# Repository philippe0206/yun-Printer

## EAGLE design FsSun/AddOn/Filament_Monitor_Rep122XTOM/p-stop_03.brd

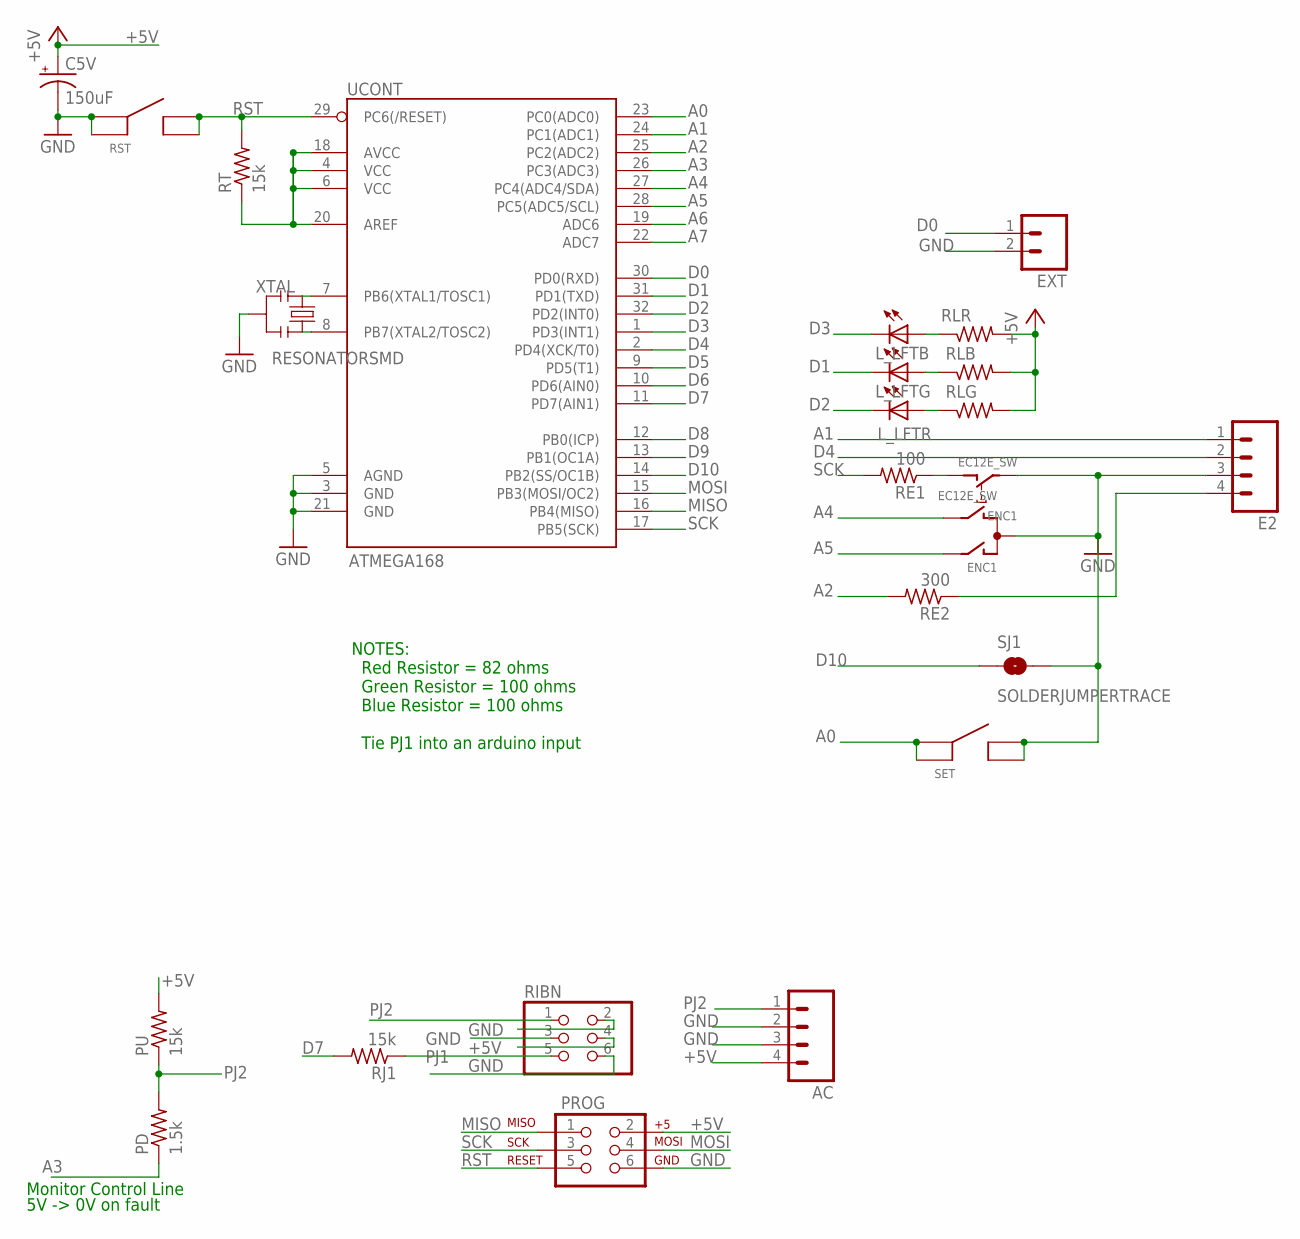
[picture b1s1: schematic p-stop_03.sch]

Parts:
AC: M04PTH; 1X04
C5V: 150uF; EIA3528
E2: M04PTH; 1X04
ENC1: EC12E_SW; ALPS_EC12E_SW
EXT: M02PTH; 1X02
L_LFT: GM5WA94310A
PD: 1.5k; MINI_MELF-0204R
PROG: AVR_SPI_PRG_6NS; 2X3-NS
PU: 15k; MINI_MELF-0204R
RE1: 100; MINI_MELF-0204R
RE2: 300; MINI_MELF-0204R
RIBN: PINHD-2X3; 2X03
RJ1: 15k; MINI_MELF-0204R
RLB: 100; MINI_MELF-0204R
RLG: 100; MINI_MELF-0204R
RLR: 100; MINI_MELF-0204R
RST: 6MM_TACT_SMD; 6MMSMDTACT
RT: 15k; MINI_MELF-0204R
SET: 6MM_TACT_SMD; 6MMSMDTACT
SJ1: SOLDERJUMPERTRACE; SJ_2S-TRACE
UCONT: ATMEGA168; TQFP32-08
XTAL: RESONATORSMD; RESONATOR-SMD

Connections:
+5V: AC.4, C5V.A (+), PROG.2, PU.2, RIBN.4, RLB.2, RLG.2, RLR.2, RT.1, UCONT.4 (VCC), UCONT.6 (VCC), UCONT.18 (AVCC), UCONT.20 (AREF)
A0: SET.P1, SET.P2, UCONT.23 (PC0(ADC0))
A1: E2.1, UCONT.24 (PC1(ADC1))
A2: RE2.2, UCONT.25 (PC2(ADC2))
A3: PD.1, UCONT.26 (PC3(ADC3))
A4: ENC1.B, UCONT.27 (PC4(ADC4/SDA))
A5: ENC1.A, UCONT.28 (PC5(ADC5/SCL))
A6: UCONT.19 (ADC6)
A7: UCONT.22 (ADC7)
D0: EXT.1, UCONT.30 (PD0(RXD))
D1: L_LFT.4 (C), UCONT.31 (PD1(TXD))
D2: L_LFT.5 (C), UCONT.32 (PD2(INT0))
D3: L_LFT.6 (C), UCONT.1 (PD3(INT1))
D4: E2.2, UCONT.2 (PD4(XCK/T0))
D5: UCONT.9 (PD5(T1))
D6: UCONT.10 (PD6(AIN0))
D7: RJ1.2, UCONT.11 (PD7(AIN1))
D8: UCONT.12 (PB0(ICP))
D9: UCONT.13 (PB1(OC1A))
D10: SJ1.1, UCONT.14 (PB2(SS/OC1B))
ENC2L: E2.4, RE2.1
GND: AC.2, AC.3, C5V.C (-), E2.3, ENC1.C, ENC1.E (2), EXT.2, PROG.6, RIBN.2, RIBN.3, RIBN.6, RST.P1, RST.P2, SET.N1, SET.N2, SJ1.2, UCONT.3 (GND), UCONT.5 (AGND), UCONT.21 (GND), XTAL.2
MISO: PROG.1, UCONT.16 (PB4(MISO))
MOSI: PROG.4, UCONT.15 (PB3(MOSI/OC2))
unnamed: UCONT.7 (PB6(XTAL1/TOSC1)), XTAL.1
unnamed: UCONT.8 (PB7(XTAL2/TOSC2)), XTAL.3
unnamed: ENC1.D (1), RE1.1
unnamed: L_LFT.1 (A), RLR.1
unnamed: L_LFT.3 (A), RLB.1
unnamed: L_LFT.2 (A), RLG.1
PJ1: RIBN.5, RJ1.1
PJ2: AC.1, PD.2, PU.1, RIBN.1
RST: PROG.5, RST.N1, RST.N2, RT.2, UCONT.29 (PC6(/RESET))
SCK: PROG.3, RE1.2, UCONT.17 (PB5(SCK))

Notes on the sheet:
NOTES: Red Resistor = 82 ohms Green Resistor = 100 ohms Blue Resistor = 100 ohms Tie PJ1 into an arduino input
Monitor Control Line
5V -> 0V on fault

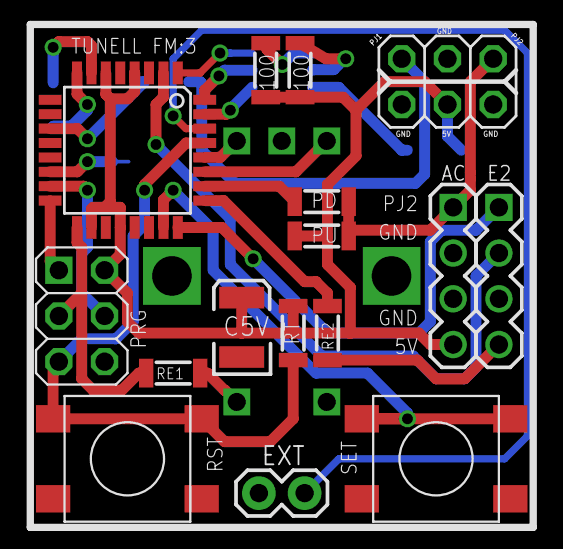
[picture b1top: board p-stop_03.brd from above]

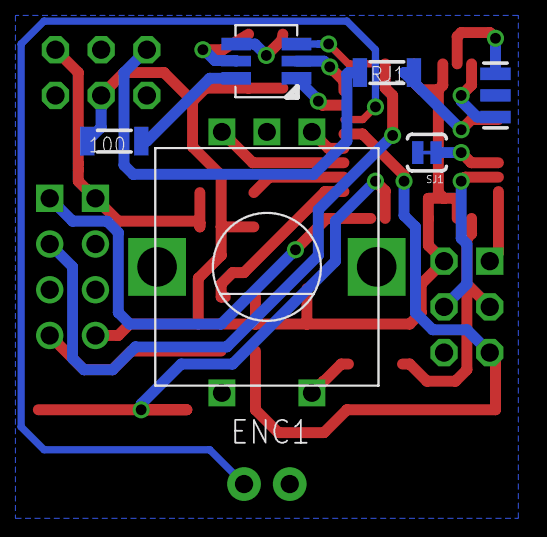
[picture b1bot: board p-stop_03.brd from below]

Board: 2 copper layers, 22 parts (6 on the bottom side), 28 nets.

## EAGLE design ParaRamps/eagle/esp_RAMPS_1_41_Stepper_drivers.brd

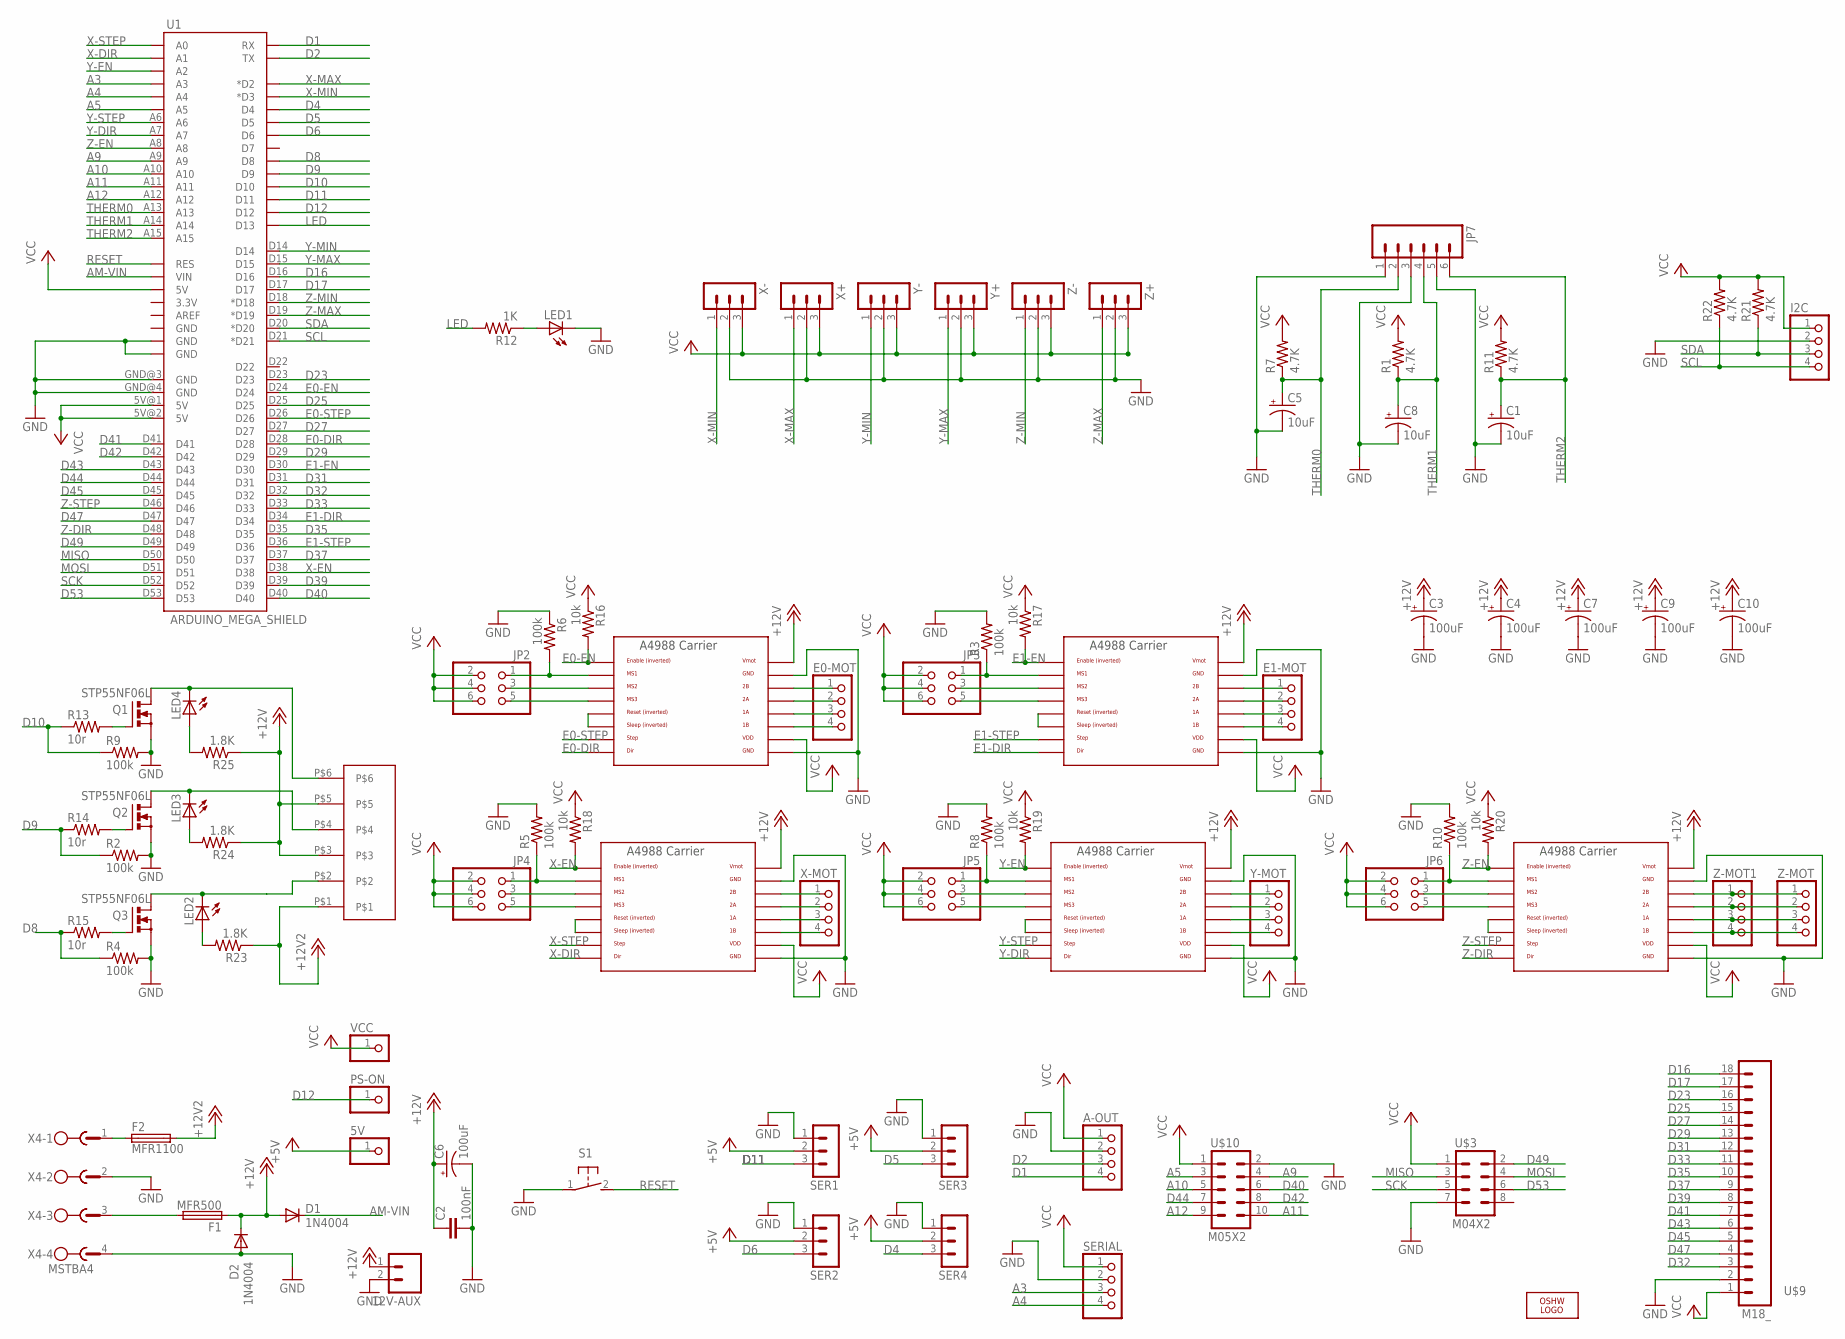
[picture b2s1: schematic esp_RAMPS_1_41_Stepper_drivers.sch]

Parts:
5V: PINHD-1X1; 1X01
12V-AUX: M02PTH; 1X02
A-OUT: PINHD-1X4; 1X04
C1, C5, C8: 10uF; 153CLV-0405
C2: 100nF; C0805
C3, C4, C6, C7, C9, C10: 100uF; 153CLV-0605
D1, D2: 1N4004; DO41-10
E0-MOT, E1-MOT: PINHD-1X4; 1X04
F1: MFR500
F2: MFR1100
I2C: PINHD-1X4; 1X04
JP2, JP3, JP4, JP5, JP6: PINHD-2X3; 2X03
JP7: M06SIP; 1X06
LED1, LED2, LED3, LED4: LEDCHIP-LED0805; CHIP-LED0805
LOGO1: OSHW_LOGO_6MILX0100-NT; OSHW_6X100_NOTEXT
PS-ON: PINHD-1X1; 1X01
Q1, Q2, Q3: STP55NF06L; TO220BV
R1, R7, R11, R21, R22: 4.7K; R0805
R2, R3, R4, R5, R6, R8, R9, R10: 100k; R0805
R12: 1K; R0805
R13, R15: 10r; R0805
R14: 10r; M0805
R16, R17, R18, R19, R20: 10k; R0805
R23, R24, R25: 1.8K; R0805
S1: 31-XX; B3F-31XX
SER1, SER2, SER3, SER4: 3PIN-HEADER
SERIAL: PINHD-1X4; 1X04
U1: ARDUINO_MEGA_SHIELD
U$2: 282837-6
U$3: M04X2; 2X4
U$4, U$5, U$6, U$7, U$8: A4988BREAKOUT
U$9: M18_; 1X18
U$10: M05X2; 2X5
VCC: PINHD-1X1; 1X01
X4: MSTBA4
X+: 3PIN-HEADER
X-: 3PIN-HEADER
X-MOT: PINHD-1X4; 1X04
Y+: 3PIN-HEADER
Y-: 3PIN-HEADER
Y-MOT: PINHD-1X4; 1X04
Z+: 3PIN-HEADER
Z-: 3PIN-HEADER
Z-MOT, Z-MOT1: PINHD-1X4; 1X04

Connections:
+5V: 5V.1, SER1.2, SER2.2, SER3.2, SER4.2
+12V: 12V-AUX.1, C2.1, C3.+, C4.+, C6.+, C7.+, C9.+, C10.+, D1.A, D2.C, F1.1, R24.1, R25.1, U$2.P$3, U$2.P$5, U$4.VMOT, U$5.VMOT, U$6.VMOT, U$7.VMOT, U$8.VMOT
+12V2: F2.2, R23.1, U$2.P$1
A3: SERIAL.3, U1.A3
A4: SERIAL.4, U1.A4
A5: U1.A5, U$10.3
A9: U1.A9, U$10.4
A10: U1.A10, U$10.5
A11: U1.A11, U$10.10
A12: U1.A12, U$10.9
AM-VIN: D1.C, U1.VIN
D1: A-OUT.4, U1.RX
D2: A-OUT.3, U1.TX
D4: SER4.3, U1.D4
D5: SER3.3, U1.D5
D6: SER2.3, U1.D6
D8: R4.1, R15.1, U1.D8
D9: R2.1, R14.1, U1.D9
D10: R9.1, R13.1, U1.D10
D11: SER1.3, U1.D11
D12: PS-ON.1, U1.D12
D16: U1.D16, U$9.18
D17: U1.D17, U$9.17
D23: U1.D23, U$9.16
D25: U1.D25, U$9.15
D27: U1.D27, U$9.14
D29: U1.D29, U$9.13
D31: U1.D31, U$9.12
D32: U1.D32, U$9.3
D33: U1.D33, U$9.11
D35: U1.D35, U$9.10
D37: U1.D37, U$9.9
D39: U1.D39, U$9.8
D40: U1.D40, U$10.6
D41: U1.D41, U$9.7
D42: U1.D42, U$10.8
D43: U1.D43, U$9.6
D44: U1.D44, U$10.7
D45: U1.D45, U$9.5
D47: U1.D47, U$9.4
D49: U1.D49, U$3.2
D53: U1.D53, U$3.6
E0-DIR: U1.D28, U$4.DIR
E0-EN: R16.2, U1.D24, U$4.EN
E0-STEP: U1.D26, U$4.STEP
E1-DIR: U1.D34, U$5.DIR
E1-EN: R17.2, U1.D30, U$5.EN
E1-STEP: U1.D36, U$5.STEP
GND: 12V-AUX.2, A-OUT.2, C1.-, C2.2, C3.-, C4.-, C5.-, C6.-, C7.-, C8.-, C9.-, C10.-, D2.A, I2C.2, JP7.1, JP7.3, JP7.5, LED1.C, Q1.S, Q2.S, Q3.S, R2.2, R3.2, R4.2, R5.2, R6.1, R8.2, R9.2, R10.2, S1.1, SER1.1, SER2.1, SER3.1, SER4.1, SERIAL.2, U1.GND@0 (GND), U1.GND@1 (GND), U1.GND@3 (GND), U1.GND@4 (GND), U$3.7, U$4.GND, U$4.GND@0 (GND), U$5.GND, U$5.GND@0 (GND), U$6.GND, U$6.GND@0 (GND), U$7.GND, U$7.GND@0 (GND), U$8.GND, U$8.GND@0 (GND), U$9.2, U$10.2, X4.2, X4.4, X+.2, X-.2, Y+.2, Y-.2, Z+.2, Z-.2
LED: R12.2, U1.D13
MISO: U1.D50, U$3.3
MOSI: U1.D51, U$3.4
unnamed: LED3.C, Q2.D, U$2.P$4
unnamed: E0-MOT.1, U$4.2B
unnamed: E0-MOT.2, U$4.2A
unnamed: JP2.1, R6.2, U$4.MS1
unnamed: JP2.5, U$4.MS3
unnamed: LED4.C, Q1.D, U$2.P$6
unnamed: U$4.RST, U$4.SLP (SLEEP)
unnamed: JP2.3, U$4.MS2
unnamed: E0-MOT.3, U$4.1A
unnamed: E0-MOT.4, U$4.1B
unnamed: E1-MOT.1, U$5.2B
unnamed: E1-MOT.2, U$5.2A
unnamed: JP4.1, R5.1, U$6.MS1
unnamed: JP4.3, U$6.MS2
unnamed: E1-MOT.3, U$5.1A
unnamed: JP5.3, U$7.MS2
unnamed: E1-MOT.4, U$5.1B
unnamed: JP4.5, U$6.MS3
unnamed: U$6.RST, U$6.SLP (SLEEP)
unnamed: U$6.2B, X-MOT.1
unnamed: U$6.2A, X-MOT.2
unnamed: U$7.RST, U$7.SLP (SLEEP)
unnamed: U$5.RST, U$5.SLP (SLEEP)
unnamed: JP3.1, R3.1, U$5.MS1
unnamed: U$6.1A, X-MOT.3
unnamed: U$6.1B, X-MOT.4
unnamed: U$7.2B, Y-MOT.1
unnamed: U$7.2A, Y-MOT.2
unnamed: U$7.1A, Y-MOT.3
unnamed: JP5.5, U$7.MS3
unnamed: LED2.A, R23.2
unnamed: JP5.1, R8.1, U$7.MS1
unnamed: JP3.5, U$5.MS3
unnamed: JP3.3, U$5.MS2
unnamed: U$7.1B, Y-MOT.4
unnamed: JP6.3, U$8.MS2
unnamed: U$8.RST, U$8.SLP (SLEEP)
unnamed: JP6.5, U$8.MS3
unnamed: JP6.1, R10.1, U$8.MS1
unnamed: U$8.2B, Z-MOT.1, Z-MOT1.1
unnamed: U$8.2A, Z-MOT.2, Z-MOT1.2
unnamed: U$8.1A, Z-MOT.3, Z-MOT1.3
unnamed: U$8.1B, Z-MOT.4, Z-MOT1.4
unnamed: LED3.A, R24.2
unnamed: LED1.A, R12.1
unnamed: Q2.G, R14.2
unnamed: Q1.G, R13.2
unnamed: Q3.G, R15.2
unnamed: LED4.A, R25.2
unnamed: LED2.C, Q3.D, U$2.P$2
unnamed: F2.1, X4.1
unnamed: F1.2, X4.3
RESET: S1.2 (S), U1.RES
SCK: U1.D52, U$3.5
SCL: I2C.4, R22.1, U1.D21 (*D21)
SDA: I2C.3, R21.1, U1.D20 (*D20)
THERM0: C5.+, JP7.2, R7.1, U1.A13
THERM1: C8.+, JP7.4, R1.1, U1.A14
THERM2: C1.+, JP7.6, R11.1, U1.A15
VCC: A-OUT.1, I2C.1, JP2.2, JP2.4, JP2.6, JP3.2, JP3.4, JP3.6, JP4.2, JP4.4, JP4.6, JP5.2, JP5.4, JP5.6, JP6.2, JP6.4, JP6.6, R1.2, R7.2, R11.2, R16.1, R17.1, R18.1, R19.1, R20.1, R21.2, R22.2, SERIAL.1, U1.5V@0 (5V), U1.5V@1 (5V), U1.5V@2 (5V), U$3.1, U$4.VDD, U$5.VDD, U$6.VDD, U$7.VDD, U$8.VDD, U$9.1, U$10.1, VCC.1, X+.3, X-.3, Y+.3, Y-.3, Z+.3, Z-.3
X-DIR: U1.A1, U$6.DIR
X-EN: R18.2, U1.D38, U$6.EN
X-MAX: U1.D2 (*D2), X+.1
X-MIN: U1.D3 (*D3), X-.1
X-STEP: U1.A0, U$6.STEP
Y-DIR: U1.A7, U$7.DIR
Y-EN: R19.2, U1.A2, U$7.EN
Y-MAX: U1.D15, Y+.1
Y-MIN: U1.D14, Y-.1
Y-STEP: U1.A6, U$7.STEP
Z-DIR: U1.D48, U$8.DIR
Z-EN: R20.2, U1.A8, U$8.EN
Z-MAX: U1.D19 (*D19), Z+.1
Z-MIN: U1.D18 (*D18), Z-.1
Z-STEP: U1.D46, U$8.STEP

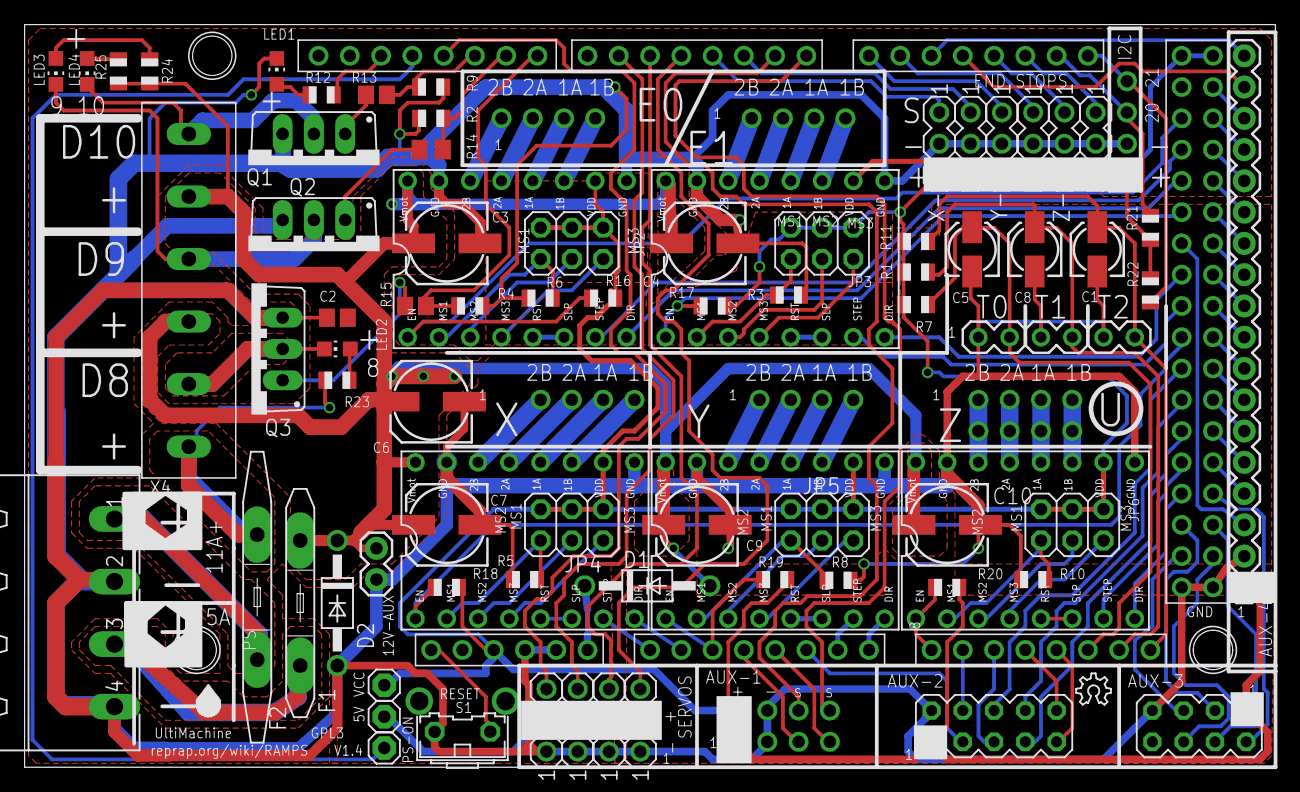
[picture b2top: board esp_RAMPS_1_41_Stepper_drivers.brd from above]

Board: 2 copper layers, 101.6 x 60.3 mm, 88 parts (0 on the bottom side), 127 nets.

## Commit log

2018-03-14 second commit

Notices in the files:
ParaRamps/eagle/esp_RAMPS_1_41_Stepper_drivers.brd:
GPL3
GPL v3
Copyright 2011 Johnny Russell - UltiMachine
parts and their libraries:
SparkFun-Connectors: Licensing: CC v3.0 Share-Alike You are welcome to use this library for commercial purposes.
